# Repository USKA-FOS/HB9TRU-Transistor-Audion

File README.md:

# Introduction

Shortwave radio, in the frequency range of 3 to 30 MHz (100 to 10 m wavelength), has lost popularity with the advent of the modern digital communication means, which are much more powerful as to the available information-carrying capacity. Nevertheless, shortwave radio has an unbeatable advantage over Internet & Co, in that it does not depend on external network resources. Shortwave radio enables global, direct point-to-point communication, which remains available when everything else fails. This is the principal reason why shortwave radio is still appreciated and used today for communication with ships and aircrafts, for world-wide commercial radio stations, as well as by the radio amateurs, who enjoy the use of certain frequency bands for their world-wide private talks.

**The present project is aimed at sensitising the public to shortwave radio.** It presents a simple-to-build and nevertheless extremely sensitive radio receiver, which can be tuned, by the choice of an appropriate, user-made coil (an experimental part!), to about every place in the shortwave- and mediumwave-radio bands. The receiver is an ***Audion*** circuit, which operates on commercially available 2 x 25 Ohm to 2 x 32 Ohm headphones or earphones, and which is powered by a single AAA cell of 1.2 V to 1.5 V voltage; these components are not critical. It is operated by merely two control knobs, noteworthy the frequency dial knob (to the left in the image, associated with a small “frequency loupe” below it) and the sensitivity regulator (to the right in the image).

The circuit relies on a two-sided PCB (the reverse side is on ground potential and serves for screening off erratic signals which would perturbate the correct functioning of the receiver), whereupon the smaller components are soldered in surface-mount-technology (SMT), using surface-mounted devices (SMD) and the larger components by through-hole-mounting (THM). Most of its components are electronic standard parts, except a few of them which are further explained below.

The frequency-determining element of the receiver is a single **LC-circuit**, consisting of a user-made coil and a built-in variable capacitor. The coil is connected to the receiver via a standard 5.08 mm 5-pin terminal-block connector (soldered socket & screw-connector plug). This allows the user to experiment and to make his own coils, corresponding to the radio bands he wants to receive (a band change corresponds to a coil change), as well as to connect an external antenna. Large-diameter coils act furthermore as antennas for magnetic fields, so that radio reception is possible with them alone, without connecting an external antenna. Details on making the coil are given further below.

Gerber files and other release files are available on the [release page](https://github.com/USKA-FOS/HB9TRU-Transistor-Audion/releases). You will also find a BOM there to order parts from [LCSC](https://www.lcsc.com/). It may be more economical to order the common parts in volume. Note that in addition to the parts on the LCSC BOM, you also need:

- [Variable capacitor CBM-443BF](https://www.aliexpress.com/item/1005005349265750.html). (CBM-433DF with a moderately higher capacity also works; the exact capacity is not critical). These capacitors have four built-in variable-capacitor-packets, 2 for AM and 2 for FM; they were formerly used in Japanese-type transistor radios. They are still available, e.g. on AliExpress. Dials with screw for these parts are also available, e.g., on AliExpress. In the present project, we connect each an AM and an FM capacitor-packet together in parallel, and then both so combined packets together in series. The resulting variable capacitor scans a range of approximately 25pF to 100pF, which is quite suitable for the present project.
- [Variable 6 pF trimmer capacitor](https://www.aliexpress.com/item/32845044847.html). The 6 pF trimmer capacitor for the frequency loupe is a Murata TZC3Z060A110A, which is actually out of production, but still commercially available in large quantities, e.g. on Aliexpress and at Mouser. A template for a knurled knob is available in the `contrib` directory for laser cutting it out of 1 mm thick plywood or Pertinax laminate. The cut-out knob can then be put onto the central screw of the soldered trimmer capacitor and fixed on it with a drop of Loctite glue.
- [Knob for the sensitivity pot](//www.aliexpress.com/item/33028853050.html): for D-shaped short shaft with 6mm diameter, as commercially available.
- Coil antennas (see next paragraph).

# Antennas

Coil antennas can be wound from insulated 1.5 mm copper wire e.g. as shown in the image above. For this purpose, lacquer-insulated “magnet wire”, as used for motor windings, or simply PVC-insulated 1.5 mm² electric installation wire can be used. In the example below, for a 40m-band antenna coil, 170 cm of wire are cut off and bent into a 3-turns coil. The coil is provisionally fixed in circular form with some pieces of jumper-wire, wound around its windings, and both coil ends are then bent out at 90°, denuded of insulation, and fixed into positions 1 and 4 of the screw-connector plug. The shape of the coil is then readjusted, and the coil is finally fixed with insulation tape.

Coils with larger or smaller diameters, and with more or fewer turns, can be made in this way. If the coil serves as an antenna, the largest possible diameter gives the best receiving performance, but the coil becomes also less handy. You probably want to opt for a compromise between coil size and receiver sensitivity. During reception, the coil should not move or rattle, in order to keep the receiving frequency stable. This is important when receiving CW or SSB stations, i.e. radio amateur emissions.

An external wire antenna (about 5 m to 10 m, or even longer) can also be connected at position 5 of the screw-connector plug. This has an advantage in electrically silent environments. In electrically polluted (i.e. urban) environments, or inside houses, a coil antenna is preferably used, because coil antennas (“magnetic field antennas”) are less sensitive to electric field pollution than wire antennas, and their directivity allows to minimise perturbations by orienting the coil appropriately. Inside houses, the best reception with a coil antenna is generally achieved close to windows. Very often, an orientation of the coil in the horizontal plane is the most favourable orientation.

# Interactive BOM

For assembly, [InteractiveHtmlBom](https://github.com/openscopeproject/InteractiveHtmlBom) was used to create a neat interactive BOM available [here](https://htmlpreview.github.io/?https://github.com/USKA-FOS/HB9TRU-Transistor-Audion/blob/main/iBOM/ibom.html).

# Circuit and theory of operation

The _Transistor Audion_ consists of the _Audion_ circuit proper, around T1, to the left side of the circuit schematic, and a three-stage AF-amplifier, based on a chain of complementary transistors T2, T3, and T4, to the right side of the circuit schematic. The _Audion_ circuit is based on work by Burkhard Kainka, DK7JD, who published it on his [web page](https://www.b-kainka.de/) (direct link to the project [here](https://www.b-kainka.de/bastel117.htm)).

It is essentially a _Colpitts oscillator_ in common-collector circuit. To see this, you have to add the transistor’s intrinsic base-emitter capacitance C<sub>BE</sub> to the circuit schematic. This capacitor is in series with C1, which puts the emitter of the transistor into the resonant circuit, realizing therewith the feedback. Through the 10k resistor R2, the emitter is fed with an adjustable potential generated by R3. For audio frequencies, C4 (10 uF) puts the opposite side of R2 to ground potential. At high frequencies, only the 1k resistor R1, connected to ground by the 2n2 capacitor C2, acts as the transistor's working resistor. At audio frequencies, however, the 10k resistor R2 acts as the working resistor. This fact must be accounted for when designing the audio filters.

The _Colpitts oscillator_ in common collector circuit is characterized by a very smooth onset of the oscillations at the critical base-emitter potential. Hence, by adjusting R3, the damping of the resonant LC circuit can be gradually removed, increasing the _Audion’s_ sensitivity and selectivity to incoming radio waves. R3 can also be used to diminish the audible intensity when receiving too strong AM stations. AM signals, which contain a carrier and one or two information-containing sidebands, are inherently demodulated at the nonlinear base-emitter diode of T1, and are then available at the emitter resistance R2.

For receiving emissions in CW or SSB, the _Audion_ is put into its self-oscillation regime by adjusting R3 beyond the point of onset of the oscillations, so as to obtain a sufficiently strong carrier-replacement BFO signal. In T1, the now available local oscillator (BFO) mixes with the received CW or SSB signals to produce an audible output. Care must be taken to keep the receiver coil mechanically stable, and to place the BFO frequency on the correct side of, and at the right distance from the SSB signal. This requires tact, because we are dealing here with some 10 Hz! Hence, use the _frequency loupe_, and sometimes even the sensitivity knob (which acts on the C<sub>BE</sub> capacity, too) to obtain a perfect adjustment when receiving SSB signals.

The audio signal passes three successive low-pass filters (R2-C2, R4-C2, and Rp4-Cp4). Each filter is designed with a corner frequency of 7.2 kHz in order to remove any trace of remaining high-frequency, which would block the entry of the following audio amplifier, in particular when receiving SSB or CW signals, where the _Audion_ is oscillating.

The three-stage amplifier is a pnp-npn-pnp _daisy-chain_ of complementary, high-beta transistors. Its operating point is adjusted through an RC feedback network consisting of R6, C6, R7, and R8, so as to set its quiet output potential to half of the supply voltage (0.7 to 0.8 V). The current amplification (beta) of each transistor is around 500, and the quiescent output current to a 50 Ohm load is 15 mA at 1.5V supply voltage. The output transistor T4 is directly driven by the collector of T3, which is a current source. T4 works therefore in a linear regime, controlling the current through the headphones or earphones, which are also forced to linear regime. T2 and T3 work in small-signal regime (ΔU/V<sub>th</sub> = ΔU/26mV << 1) and are thus linear as well. A collector resistance of 10k (R5) has been added at T2, in order to lower its input resistance.

# Assembly

Check out our [assembly video on youtube](https://www.youtube.com/watch?v=jhC7QUwKuIA)!

Assembly of the _Transistor Audion_ is straightforward. First, all SMD parts are soldered onto the PCB. To this purpose, a soldering iron having a point-shaped tip and temperature control (320°C), a pair of point-shaped electronic tweezers, and 0.3 mm or 0.5 mm flux-cored soldering wire are required. A 10 % solution of rosin in isopropanol, a good working loupe or a binocular loupe, a paper cutter, a desoldering pump, and a tweezer-shaped impedance meter are helpful too (but not necessarily required), as well as a clean and clear table surface. SMD components are soooo small...

SMD components are supplied in reel form, i.e. each individual component is contained in a small cavity in a tape on a reel, and the cavity is covered with a plastic foil. 0805 components are 2 mm x 1.25 mm in size, at varying thickness, depending on the component. When purchasing SMD components, one obtains parts (cut strips) of such tape/reel.

The minimalist’s way to assemble the circuit is to first paint the surface of the PCB, where the components are to be soldered on, with the 10 % rosin solution and to let it dry. Then, one by one, open the SMD component’s cavities by taking off the plastic foil with the paper cutter and the tweezers. Take the SMD component out, and hold it with the tweezers, feet down, in correct position onto the PCB (you need some dexterity in both your hands for doing so), and take, with your other hand, a small drop of solder from the 0.3 mm or 0.5 mm solder wire onto the tip of your soldering iron and shortly tip with it onto a first foot of your SMD component. Soldered! Now, do the same for the second foot (and the further feet) of your SMD component. Proceed on until all SMD components are soldered on.

Now solder in the classical, “through hole” components. For this purpose, free them first, if needed, from all screwed-on or pushed-on accessories, to get them as handy as possible. Then use 1 mm flux-cored soldering wire. First bend the 6 connecting leads of the variable capacitor downwards in L-shape, and shorten them appropriately, so as to fit the 6 “landing pads” on the PCB. Solder the variable capacitor tightly onto the six “landing pads”, which serve also for fixing the variable capacitor to the PCB. Now solder tighly in the right-angle Terminal Block connector socket (to this aim, solder a first contact, then, remelting the solder, push the socket tightly onto the PCB and let harden the solder. Then solder the remaining contacts). Then solder in the AAA battery holder (pay attention to the polarity!), and cut off the excessive connecting wires. Finally solder in the Headphones/Earphones jack and the 10K potentiometer (its insertion into the PCB is somewhat hard; just gently push, exerting the necessary force).

To finish the assembly, screw the large dial onto the variable capacitor, and set on the knurled knob onto the central screw of the trimmer capacitor and fix it there with a drop of Loctite. Put as well the potentiometer knob onto the D-shaped shaft, and plug in a coil.

# Operation
Insert a AAA-battery or cell, and plug in a pair of earphones or headphones of 2 x 25 Ohm or 2 x 32 Ohm impedance, as well as the coil for the desired frequency range. Set the frequency dial to the low-frequency end (left). From the minimum position (to the left) increase the sensitivity, until you hear a sudden increase of the background noise. This is the onset of the oscillator. Now slowly scan with the frequency dial through the band. At some points you hear “blips”, i.e. HF-carriers, or distorted voices. This may be an AM station. Reduce the sensitivity to the point where the oscillations vanish. You may now tune in the AM station, as well as the stations surrounding it, if there are such. You may need to iteratively adjust the frequency dial and the sensitivity pot, because the onset of the oscillations varies somewhat with the frequency. For receiving weak AM stations, you may need to move the sensitivity pot very slightly into the oscillation regime, where you hear a strong whistle due to the presence of the carrier signal. Fine-tune now the frequency to make coincide your BFO with the carrier of the AM station; the BFO will then synchronize with the carrier and you only hear the demodulated AM signal.

For receiving CW or SSB stations, move the sensitivity pot somewhat farther into the oscillation regime, such that your BFO no longer synchronizes with the carrier. You may now set your frequency dial aside a CW signal or aside an SSB signal, to listen to the transmission. Radio amateurs use Lower Sideband modulation (LSB) on the lower bands (up to including 40m), and Upper Sideband modulation (USB) on the higher bands (from 30m upward, i.e. 20m, 15m, etc.). For the demodulation of LSB, the BFO must be set slightly above the signal, and adjusted so as to avoid “Mikey Mouse” (BFO too high) or scrambled voices (BFO too low). For the demodulation of USB, the BFO must be set slightly below the signal, and adjusted accordingly. Given that the filter of the present receiver is quite wide (7.2 kHz above and below the BFO) one often hears other stations in “Mikey Mouse” or scrambled voices along with the desired station. It is also quite frequent that one only hears one part of a radio amateur conversation, because you may have good radio propagation to one of the two stations only. Propagation conditions on shortwaves are often unstable; they noteworthy depend on the sun radiation and on other factors; hence, if you have heard one station speaking, just wait and listen, whether the other one comes up, too, on the same frequency. Sometimes there are also multiple stations conversing on the same frequency simultaneously.

The best sites for shortwave reception are mountain tops. So, you might be tempted to try out your receiver on a hike to a mountain top. The “day-bands” are from 5 MHz upwards (including the 20 m and the 15 m amateur bands). During night, the lower frequencies propagate well; the “night-bands” are from 1 MHz to about 12 MHz (including the 160 m and the 80 m amateur bands). Between 5 MHz and 12 MHz are the “day-and-night-bands” (many commercial radio bands, and noteworthy the 40m and the 30m amateur bands). A detailed list of [Commercial](https://en.wikipedia.org/wiki/Broadcast_band) and [amateur radio bands](https://en.wikipedia.org/wiki/Amateur_radio_frequency_allocations#Band_characteristics) can be found, e.g., on Wikipedia (using the aforementioned hyperlinks) as well as in the file `contrib/Broadcast and Amateur Radio Bands.docx`.

# License

This project was created using [KiCad](https://www.kicad.org/) version 6.0.11 and is released in the public domain under the CC0 license.

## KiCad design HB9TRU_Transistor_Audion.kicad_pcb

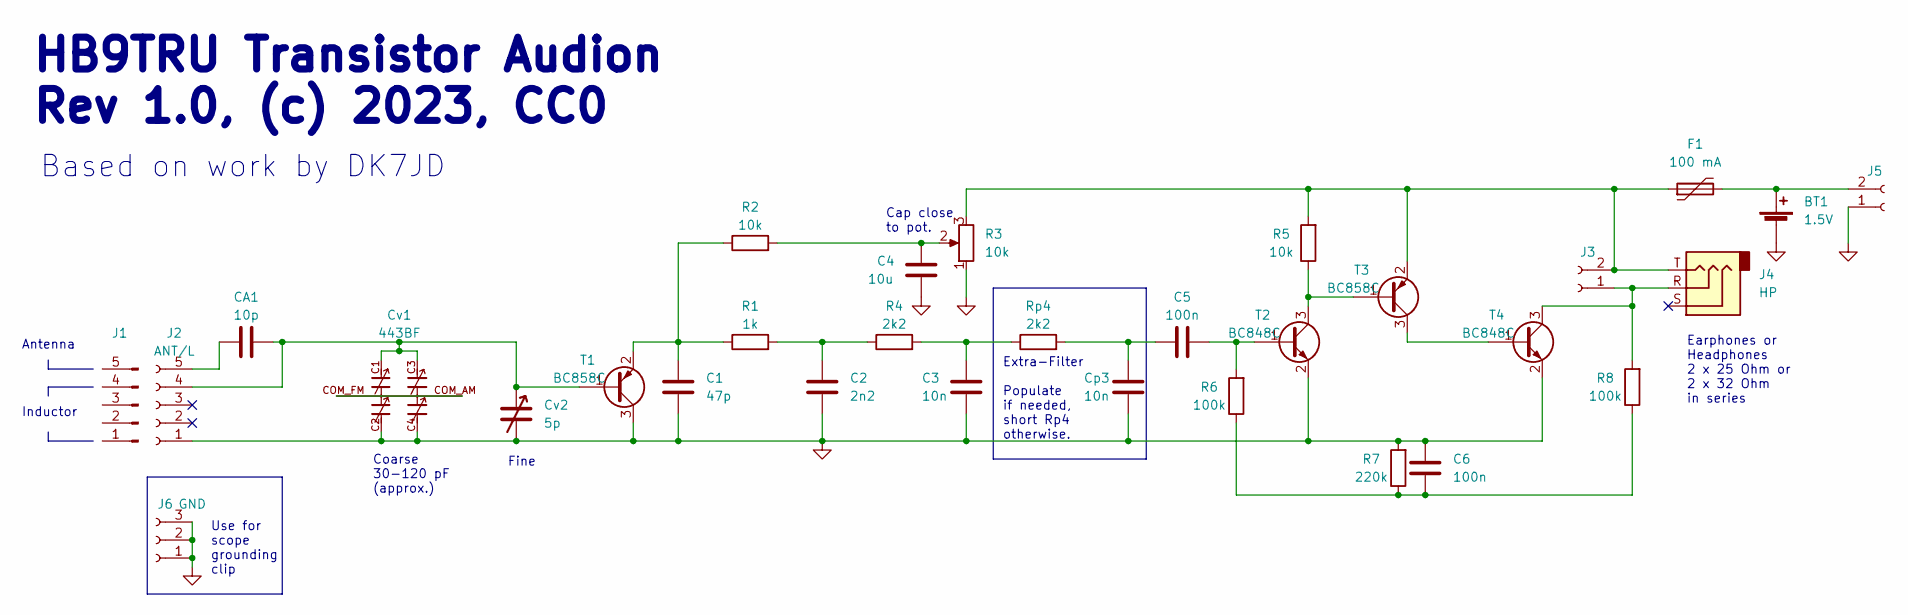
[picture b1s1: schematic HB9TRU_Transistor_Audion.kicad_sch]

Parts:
BT1: 1.5V; BatteryHolder_Keystone_2466_1xAAA; LCSC C5290189
C1: 47p; C_0805_2012Metric_Pad1.18x1.45mm_HandSolder; LCSC C525291
C2: 2n2; C_0805_2012Metric_Pad1.18x1.45mm_HandSolder; LCSC C525288
C3: 10n; C_0805_2012Metric_Pad1.18x1.45mm_HandSolder; LCSC C237168
C4: 10u; C_0805_2012Metric_Pad1.18x1.45mm_HandSolder; LCSC C17024
C5, C6: 100n; C_0805_2012Metric_Pad1.18x1.45mm_HandSolder; LCSC C525005
CA1: 10p; C_0805_2012Metric_Pad1.18x1.45mm_HandSolder; LCSC C313093
Cp3: 10n; C_0805_2012Metric_Pad1.18x1.45mm_HandSolder; LCSC C237168
Cv1: 443BF; 443BF_SMD
Cv2: 5p; C_Trimmer_Murata_TZC3
F1: 100 mA; R_0805_2012Metric_Pad1.20x1.40mm_HandSolder; LCSC C3035895
J1: Conn_01x05_Male; LCSC C5187915
J2: ANT/L; PhoenixContact_MSTBA_2,5_5-G-5,08_1x05_P5.08mm_Horizontal; LCSC C5188022
J3: HP; PinHeader_1x02_P2.54mm_Vertical
J4: HP; Jack_3.5mm_CUI_SJ1-3525N_Horizontal; LCSC C16684
J5: 1V5; PinHeader_1x02_P2.54mm_Vertical
J6: GND; PinHeader_1x03_P2.54mm_Vertical
R1: 1k; R_0805_2012Metric_Pad1.20x1.40mm_HandSolder; LCSC C2889437
R2, R5: 10k; R_0805_2012Metric_Pad1.20x1.40mm_HandSolder; LCSC C2889436
R3: 10k; Potentiometer_Alps_RK09K_Single_Vertical; LCSC C388854
R4: 2k2; R_0805_2012Metric_Pad1.20x1.40mm_HandSolder; LCSC C17520
R6, R8: 100k; R_0805_2012Metric_Pad1.20x1.40mm_HandSolder; LCSC C2907217
R7: 220k; R_0805_2012Metric_Pad1.20x1.40mm_HandSolder; LCSC C5140137
Rp4: 2k2; R_0805_2012Metric_Pad1.20x1.40mm_HandSolder; LCSC C17520
T1, T3: BC858C; SOT-23; LCSC C181149
T2, T4: BC848C; SOT-23; LCSC C181143

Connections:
GND: BT1.2 (-), C1.1, C2.1, C3.1, C4.1, C6.2, Cp3.1, Cv1.C2, Cv1.C4, Cv2.2, J2.1, J5.1, J6.1, J6.2, J6.3, R3.1, R7.2, T1.3 (C), T2.2 (E), T4.2 (E)
unnamed: BT1.1 (+), F1.2, J5.2
unnamed: C1.2, R1.1, R2.1, T1.2 (E)
unnamed: C2.2, R1.2, R4.1
unnamed: C3.2, R4.2, Rp4.1
unnamed: C4.2, R2.2, R3.2
unnamed: C5.1, Cp3.2, Rp4.2
unnamed: C5.2, R6.2, T2.1 (B)
unnamed: C6.1, R6.1, R7.1, R8.1
unnamed: CA1.1, Cv1.C1, Cv1.C3, Cv2.1, J2.4, T1.1 (B)
unnamed: CA1.2, J2.5
unnamed: Cv1.COM_AM, Cv1.COM_FM
unnamed: F1.1, J3.2, J4.T, R3.3, R5.2, T3.2 (E)
unnamed: J3.1, J4.R, R8.2, T4.3 (C)
unnamed: R5.1, T2.3 (C), T3.1 (B)
unnamed: T3.3 (C), T4.1 (B)

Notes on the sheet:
Use for scope grounding clip
Based on work by DK7JD
HB9TRU Transistor Audion Rev 1.0, (c) 2023, CC0
Inductor
Extra-Filter Populate if needed, short Rp4 otherwise.
Cap close to pot.
Antenna
Earphones or Headphones 2 x 25 Ohm or 2 x 32 Ohm in series
Coarse 30-120 pF (approx.)
Fine

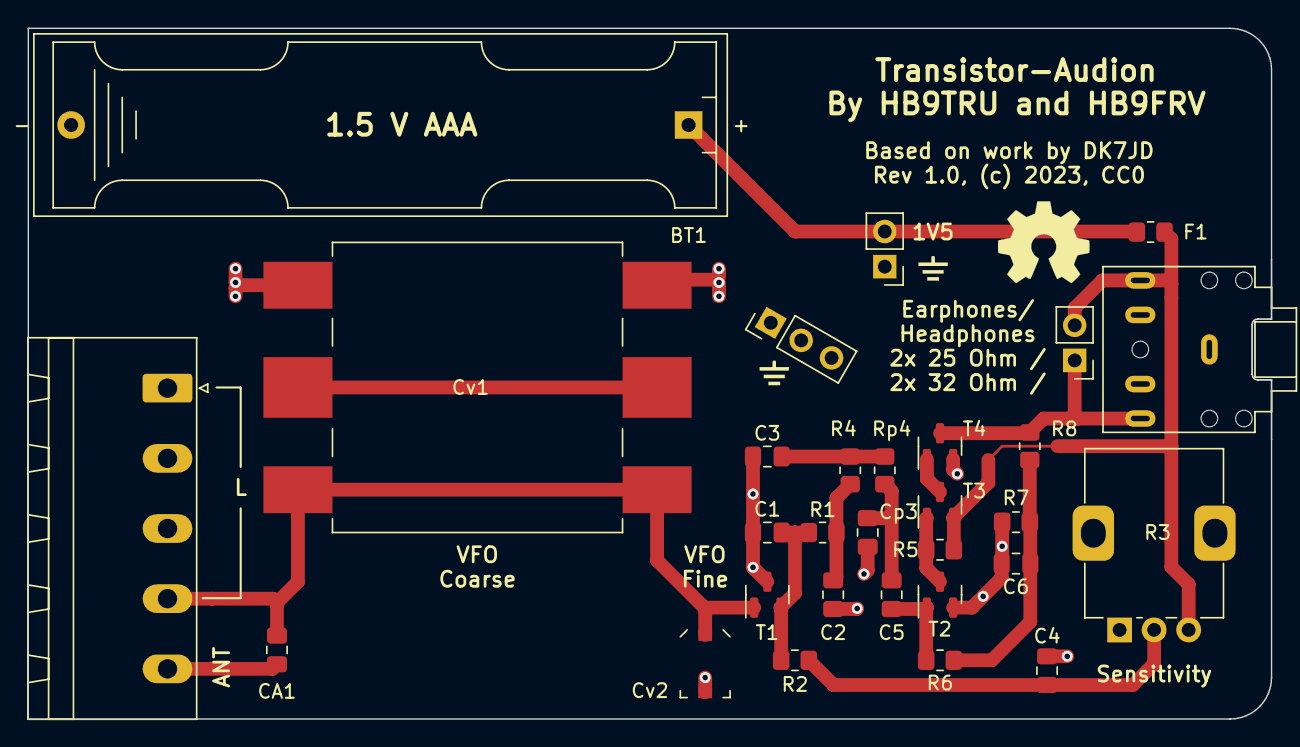
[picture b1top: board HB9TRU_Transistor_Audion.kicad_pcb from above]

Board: 2 copper layers, 90.0 x 50.0 mm, 32 parts (0 on the bottom side), 16 nets.

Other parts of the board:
GND: GND
GND#2: GND

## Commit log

2023-04-04 Adding contrib/Broadcast and Amateur Radio Bands.docx and README entry
    Original source of the tables:
    https://en.wikipedia.org/wiki/Broadcast_band
    https://en.wikipedia.org/wiki/Amateur_radio_frequency_allocations#Band_characteristics
2023-04-05 README.md: Improved wording
2023-04-05 README.md: Further improvements of wording (minor)
2023-06-08 Linking assembly video in README.md

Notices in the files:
README.md:
License:
This project was created using [KiCad](https://www.kicad.org/) version 6.0.11 and is released in the public domain under the CC0 license.
